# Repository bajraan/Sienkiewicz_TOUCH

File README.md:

# Sienkiewicz PCB

Sienkiewicz PCB project realized in KiCAD 9

> 🔗 Project main system repository: https://github.com/bajraan/Sienkiewicz__3ART00__SYSTEM

<h1 align="center">3ART12 TOUCH</h1>

<p align="center" width="100%">
  
</p>

***

<p align="center">
  
&nbsp; &nbsp; &nbsp; &nbsp;
  
</p>

***

## SPECIFICATIONS

| Parameter | Value | 
| --- | --- |
| Dimensions | 38.0 × 38.0 mm |

***

## DIRECTORY STRUCTURE

    .
    ├─ Computations       # Misc calculations
    ├─ HTML               # HTML files for generated webpage
    ├─ Images             # Pictures and renders
    │
    ├─ kibot_resources    # External resources for KiBot
    │  ├─ colors          # Color theme for KiCad
    │  ├─ fonts           # Fonts used in the project
    │  ├─ scripts         # External scripts used with KiBot
    │  └─ templates       # Templates for KiBot generated reports
    │
    ├─ kibot_yaml         # KiBot YAML config files
    ├─ KiRI               # KiRI (PCB diff viewer) files
    │
    ├─ lib                # KiCad footprint and symbol libraries
    │  ├─ 3d_models       # Component 3D models
    │  ├─ lib_fp          # Footprint libraries
    │  └─ lib_sym         # Symbol libraries
    │
    ├─ Logos              # Logos
    │
    ├─ Manufacturing      # Assembly and fabrication documents
    │  ├─ Assembly        # Assembly documents (BoM, pos, notes)
    │  │
    │  └─ Fabrication     # Fabrication documents (ZIP, notes)
    │     ├─ Drill Tables # CSV drill tables
    │     └─ Gerbers      # Gerbers
    │
    ├─ Report             # Reports for ERC/DRC
    ├─ Schematic          # PDF of schematic
    ├─ Templates          # Title block templates
    ├─ Testing
    │  └─ Testpoints      # Testpoints tables      
    │
    └─ Variants           # Outputs for assembly variants

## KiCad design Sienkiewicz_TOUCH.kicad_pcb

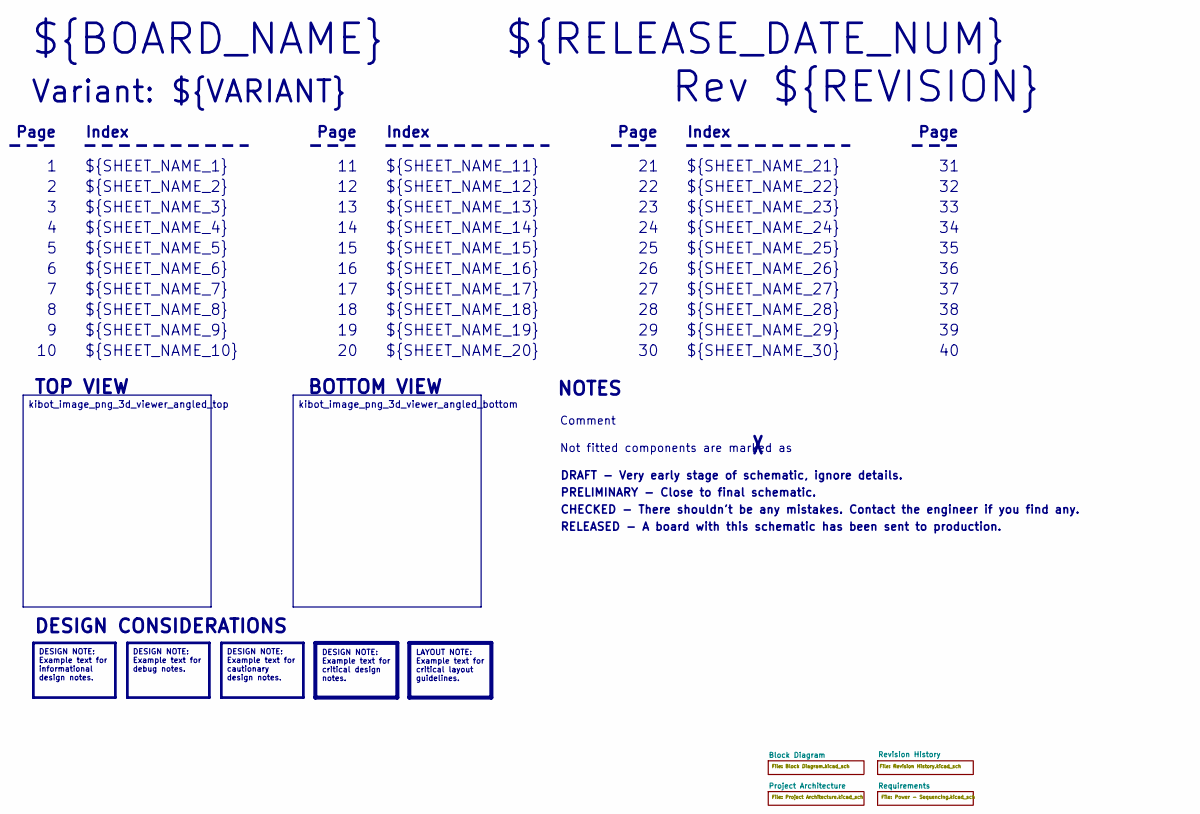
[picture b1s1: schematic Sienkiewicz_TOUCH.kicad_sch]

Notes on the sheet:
Variant: ${VARIANT}
RELEASED - A board with this schematic has been sent to production.
${SHEET_NAME_24}
Index
Page
PRELIMINARY - Close to final schematic.
${SHEET_NAME_22}
DRAFT - Very early stage of schematic, ignore details.
${SHEET_NAME_12}
${SHEET_NAME_8}
${SHEET_NAME_2}
${SHEET_NAME_5}
${SHEET_NAME_20}
${SHEET_NAME_23}
${RELEASE_DATE_NUM}
Not fitted components are marked as
${SHEET_NAME_11}
${SHEET_NAME_6}
${SHEET_NAME_26}
Rev ${REVISION}
${SHEET_NAME_15}
CHECKED - There shouldn't be any mistakes. Contact the engineer if you find any.
BOTTOM VIEW
${SHEET_NAME_14}
${SHEET_NAME_21}
${SHEET_NAME_17}
${SHEET_NAME_18}
${SHEET_NAME_7}
${BOARD_NAME}
NOTES
${SHEET_NAME_1}
${SHEET_NAME_9}
${SHEET_NAME_29}
${SHEET_NAME_16}
${SHEET_NAME_3}
${SHEET_NAME_19}
Comment
TOP VIEW
${SHEET_NAME_10}
${SHEET_NAME_28}

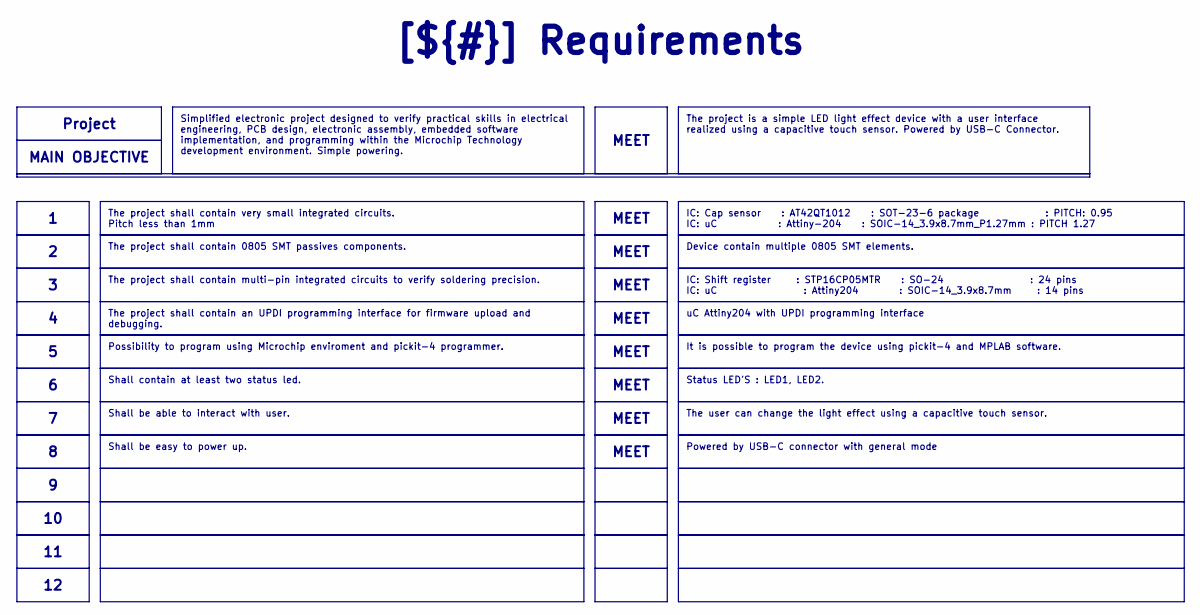
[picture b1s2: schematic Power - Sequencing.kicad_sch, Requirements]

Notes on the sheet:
Powered by USB-C connector with general mode
IC: Cap sensor : AT42QT1012 : SOT-23-6 package : PITCH: 0.95 IC: uC : Attiny-204 : SOIC-14_3.9x8.7mm_P1.27mm : PITCH 1.27
Simplified electronic project designed to verify practical skills in electrical engineering, PCB design, electronic assembly, embedded software implementation, and programming within the Microchip Technology development environment. Simple powering.
Shall contain at least two status led.
The project shall contain very small integrated circuits. Pitch less than 1mm
uC Attiny204 with UPDI programming interface
Status LED'S : LED1, LED2.
MEET
Shall be easy to power up.
Project
The project shall contain an UPDI programming interface for firmware upload and debugging.
[${#}] ${TITLE}
IC: Shift register : STP16CP05MTR : SO-24 : 24 pins IC: uC : Attiny204 : SOIC-14_3.9x8.7mm : 14 pins
It is possible to program the device using pickit-4 and MPLAB software.
MAIN OBJECTIVE
The user can change the light effect using a capacitive touch sensor.
The project shall contain multi-pin integrated circuits to verify soldering precision.
The project shall contain 0805 SMT passives components.
Device contain multiple 0805 SMT elements.
Possibility to program using Microchip enviroment and pickit-4 programmer.
Shall be able to interact with user.
The project is a simple LED light effect device with a user interface realized using a capacitive touch sensor. Powered by USB-C Connector.

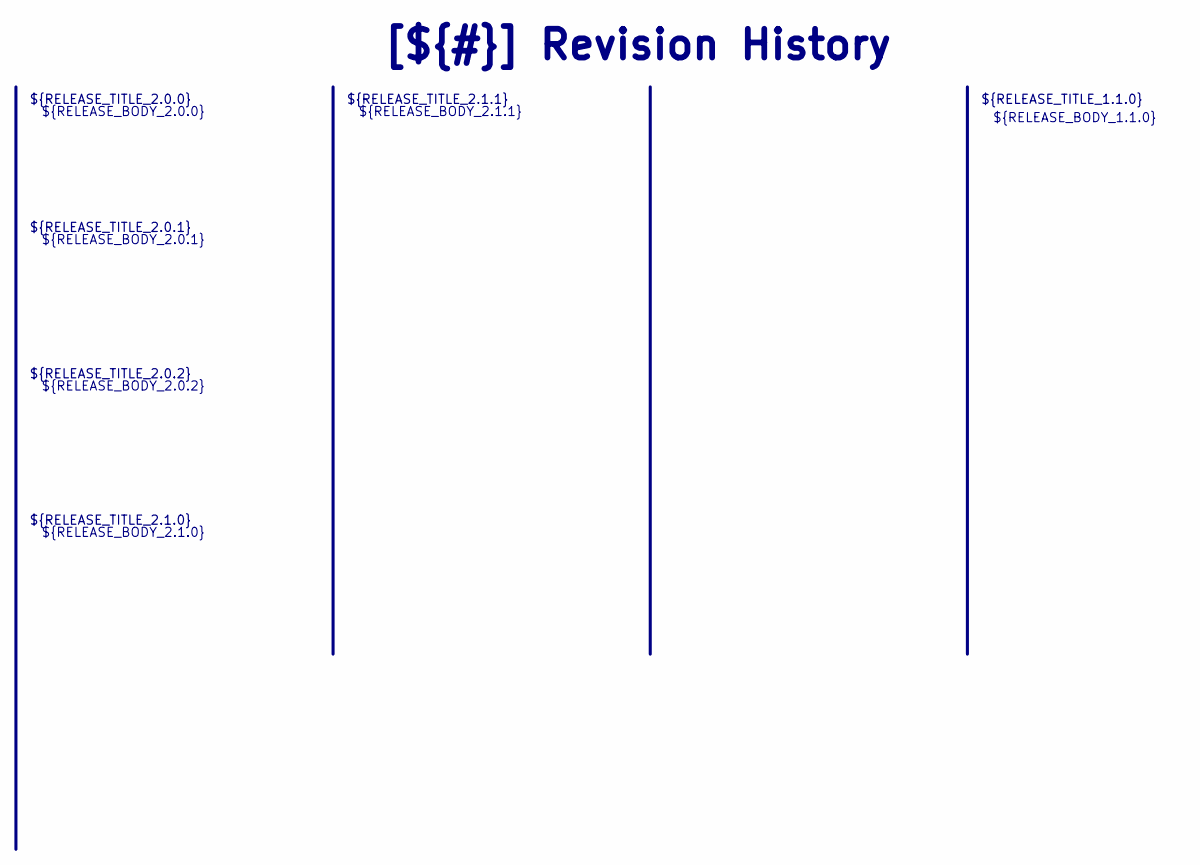
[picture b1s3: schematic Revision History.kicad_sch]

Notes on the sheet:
${RELEASE_BODY_1.1.0}
${RELEASE_BODY_2.1.1}
[${#}] ${TITLE}
${RELEASE_BODY_2.0.0}
${RELEASE_TITLE_2.1.1}
${RELEASE_BODY_2.1.0}
${RELEASE_TITLE_2.0.2}
${RELEASE_TITLE_2.1.0}
${RELEASE_BODY_2.0.2}
${RELEASE_BODY_2.0.1}
${RELEASE_TITLE_2.0.0}
${RELEASE_TITLE_2.0.1}
${RELEASE_TITLE_1.1.0}

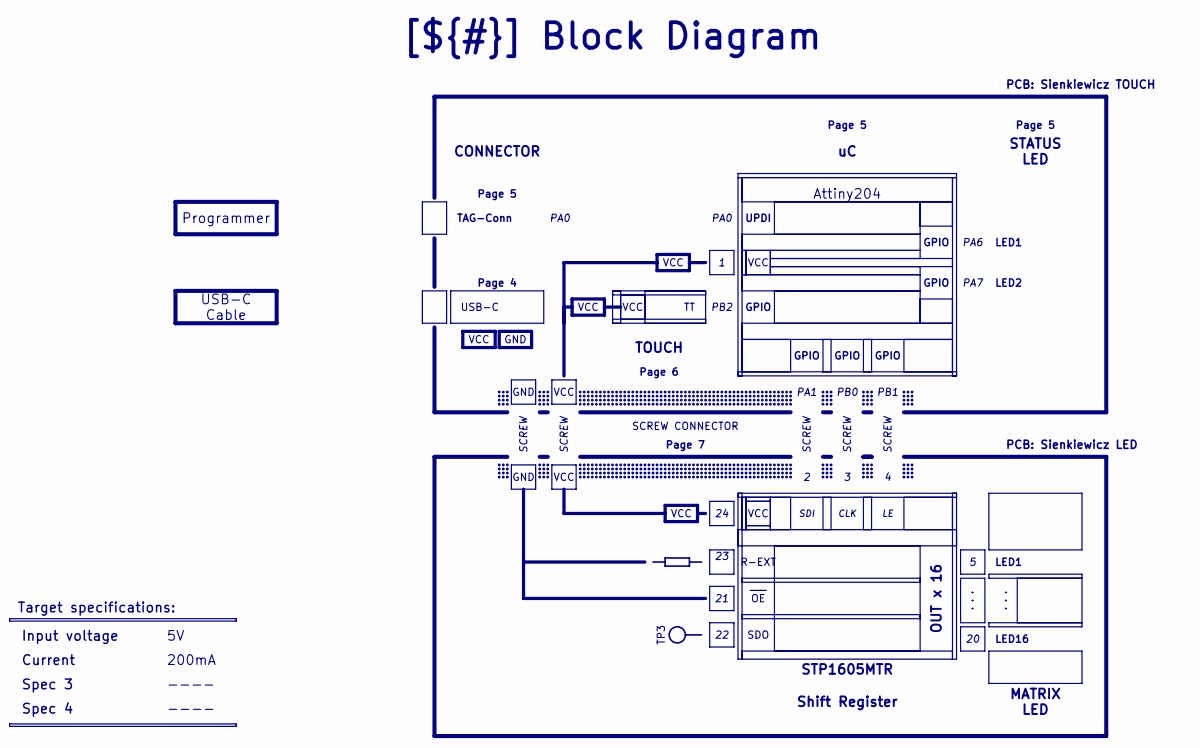
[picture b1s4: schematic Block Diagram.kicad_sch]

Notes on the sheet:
PCB: Sienkiewicz LED
PCB: Sienkiewicz TOUCH
TP3
PB1
Page 5
STATUS LED
GND
. . .
Spec 4
LED2
VCC
USB-C Cable
----
STP1605MTR
SCREW
GPIO
LED1
R-EXT
TAG-Conn
PA7
Shift Register
CLK
[${#}] ${TITLE}
200mA
Input voltage
TOUCH
Page 6
CONNECTOR
SCREW CONNECTOR
Target specifications:
Programmer
Attiny204
Page 4
PA1
Spec 3
MATRIX LED
Current
Page 7
PB0
PA0

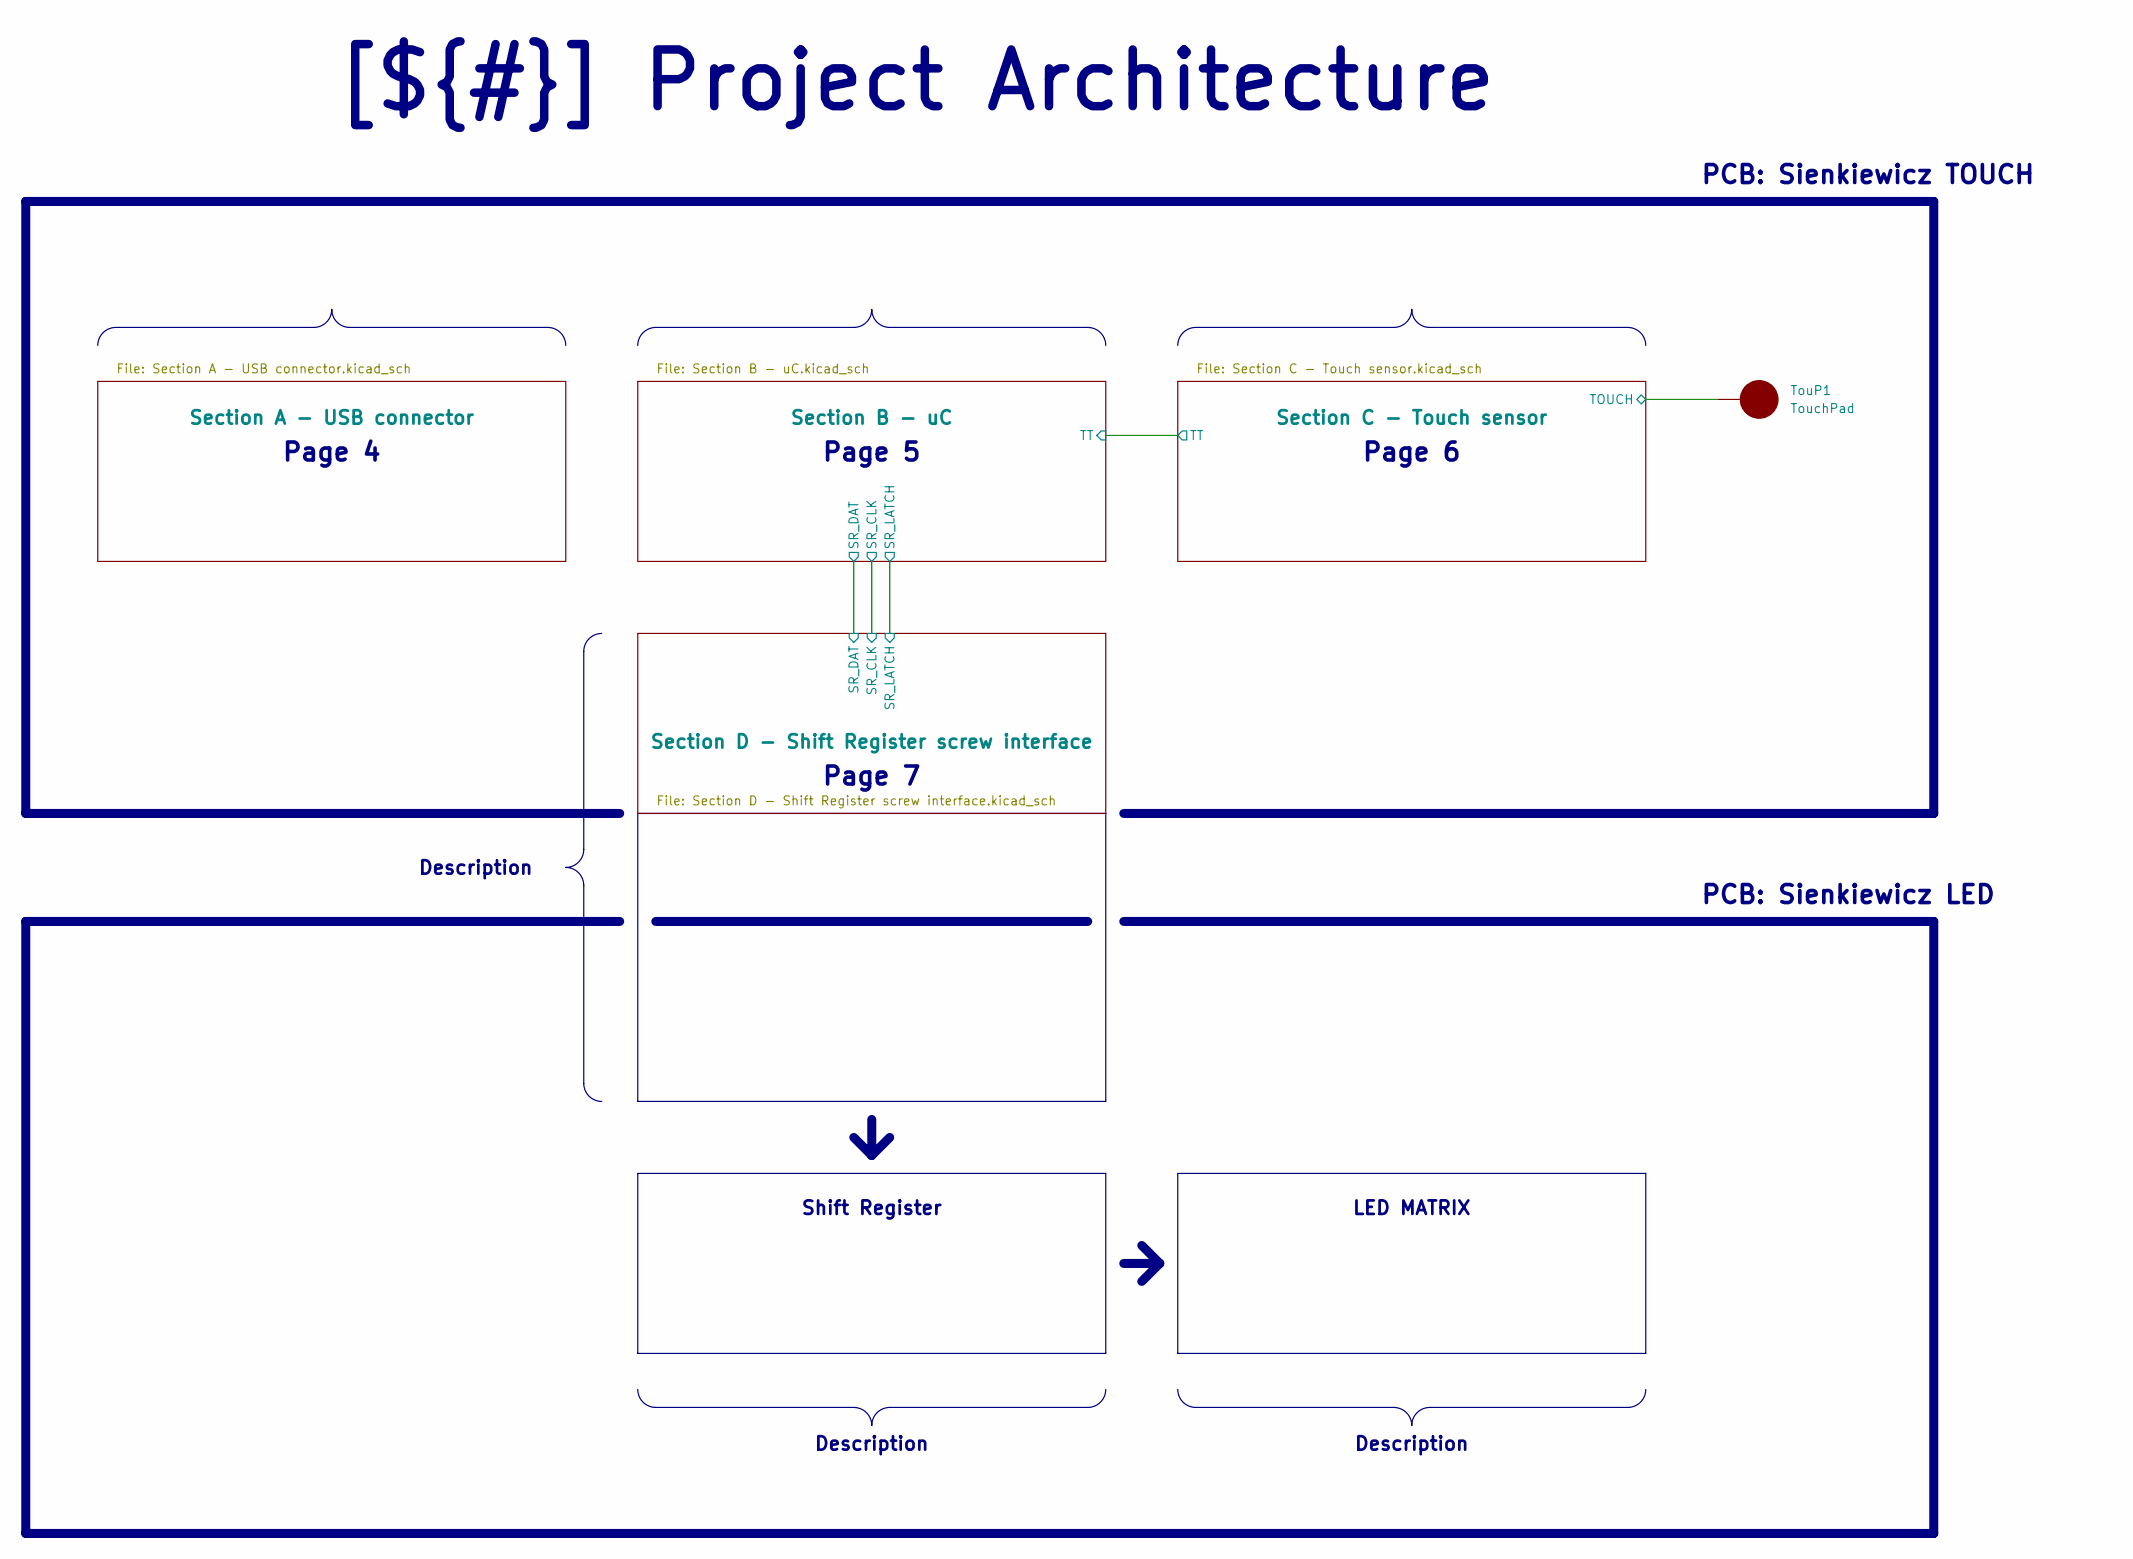
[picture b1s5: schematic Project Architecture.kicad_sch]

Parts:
TouP1: TouchPad; TouchPAD

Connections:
/Project Architecture/Section C - Touch sensor/TOUCH: TouP1.1 (TOUCH); also elsewhere on the board

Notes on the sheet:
LED MATRIX
Page 6
Shift Register
Page 7
Page 5
PCB: Sienkiewicz LED
PCB: Sienkiewicz TOUCH
Page 4
Description
[${#}] ${TITLE}

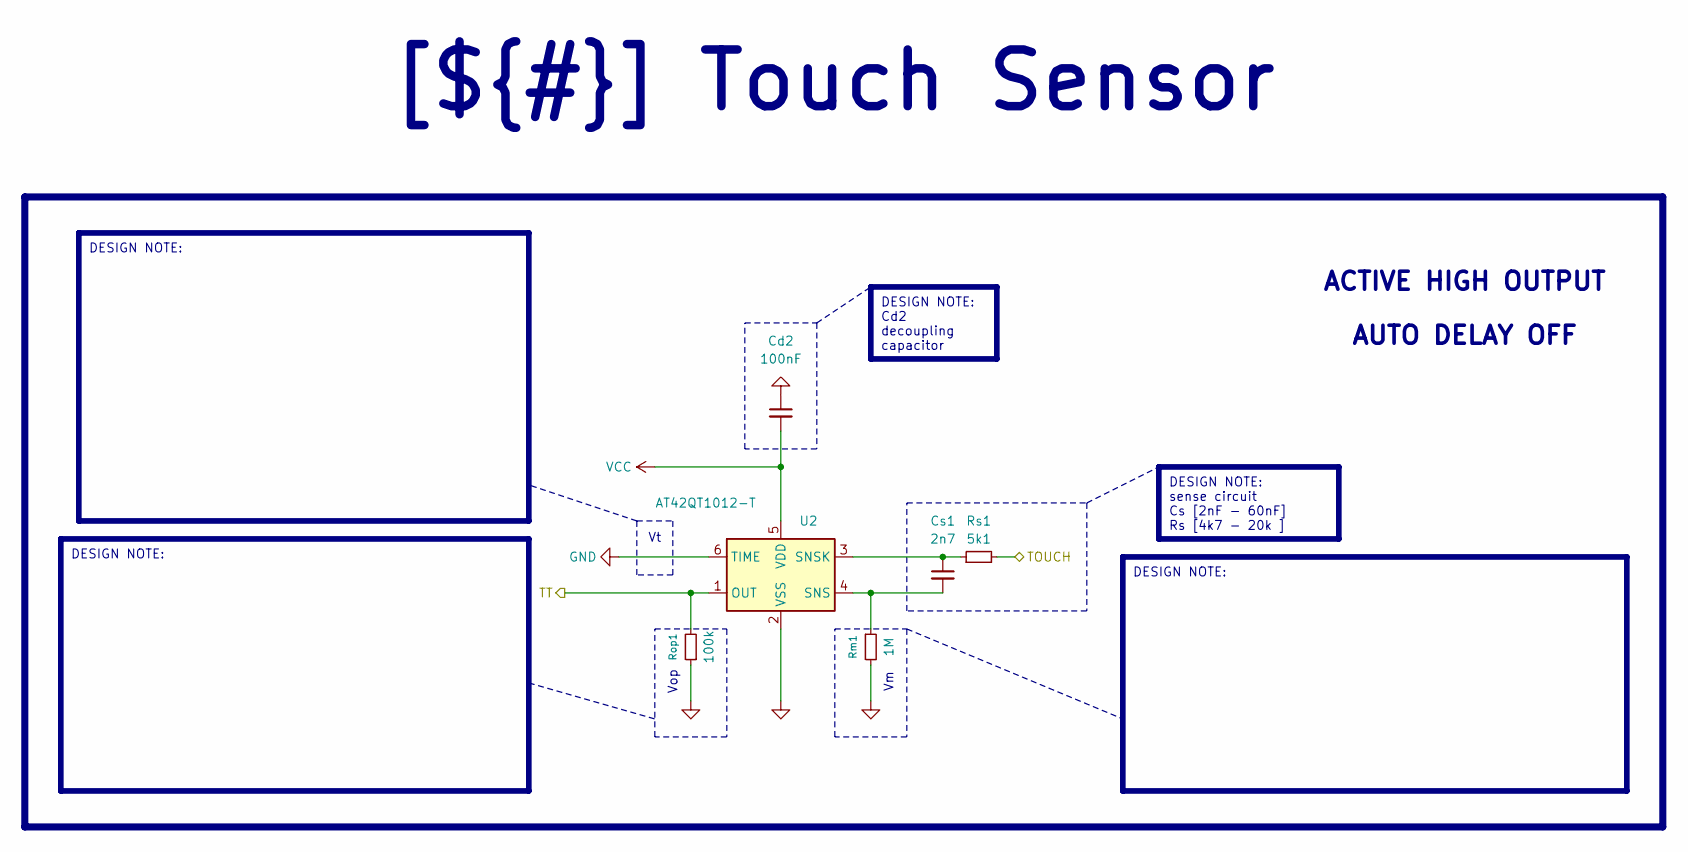
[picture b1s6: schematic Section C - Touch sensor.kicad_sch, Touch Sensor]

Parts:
Cd2: 100nF; C_1210_3225Metric
Cs1: 2n7; C_0805_2012Metric
Rm1: 1M; R_0805_2012Metric
Rop1: 100k; R_0805_2012Metric
Rs1: 5k1; R_0805_2012Metric
U2: AT42QT1012-T; SOT-23-6

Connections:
/Project Architecture/Section B - uC/TT: Rop1.2, U2.1 (OUT); also elsewhere on the board
/Project Architecture/Section C - Touch sensor/TOUCH: Rs1.2; also elsewhere on the board
GND: Cd2.1, Rm1.2, Rop1.1, U2.2 (VSS), U2.6 (TIME); also elsewhere on the board
unnamed: Cs1.2, Rm1.1, U2.4 (SNS)
unnamed: Cs1.1, Rs1.1, U2.3 (SNSK)
VCC: Cd2.2, U2.5 (VDD); also elsewhere on the board

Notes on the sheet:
Vop
DESIGN NOTE:
DESIGN NOTE: Cd2 decoupling capacitor
[${#}] ${TITLE}
DESIGN NOTE:
AUTO DELAY OFF
DESIGN NOTE: sense circuit Cs [2nF - 60nF] Rs [4k7 - 20k ]
ACTIVE HIGH OUTPUT

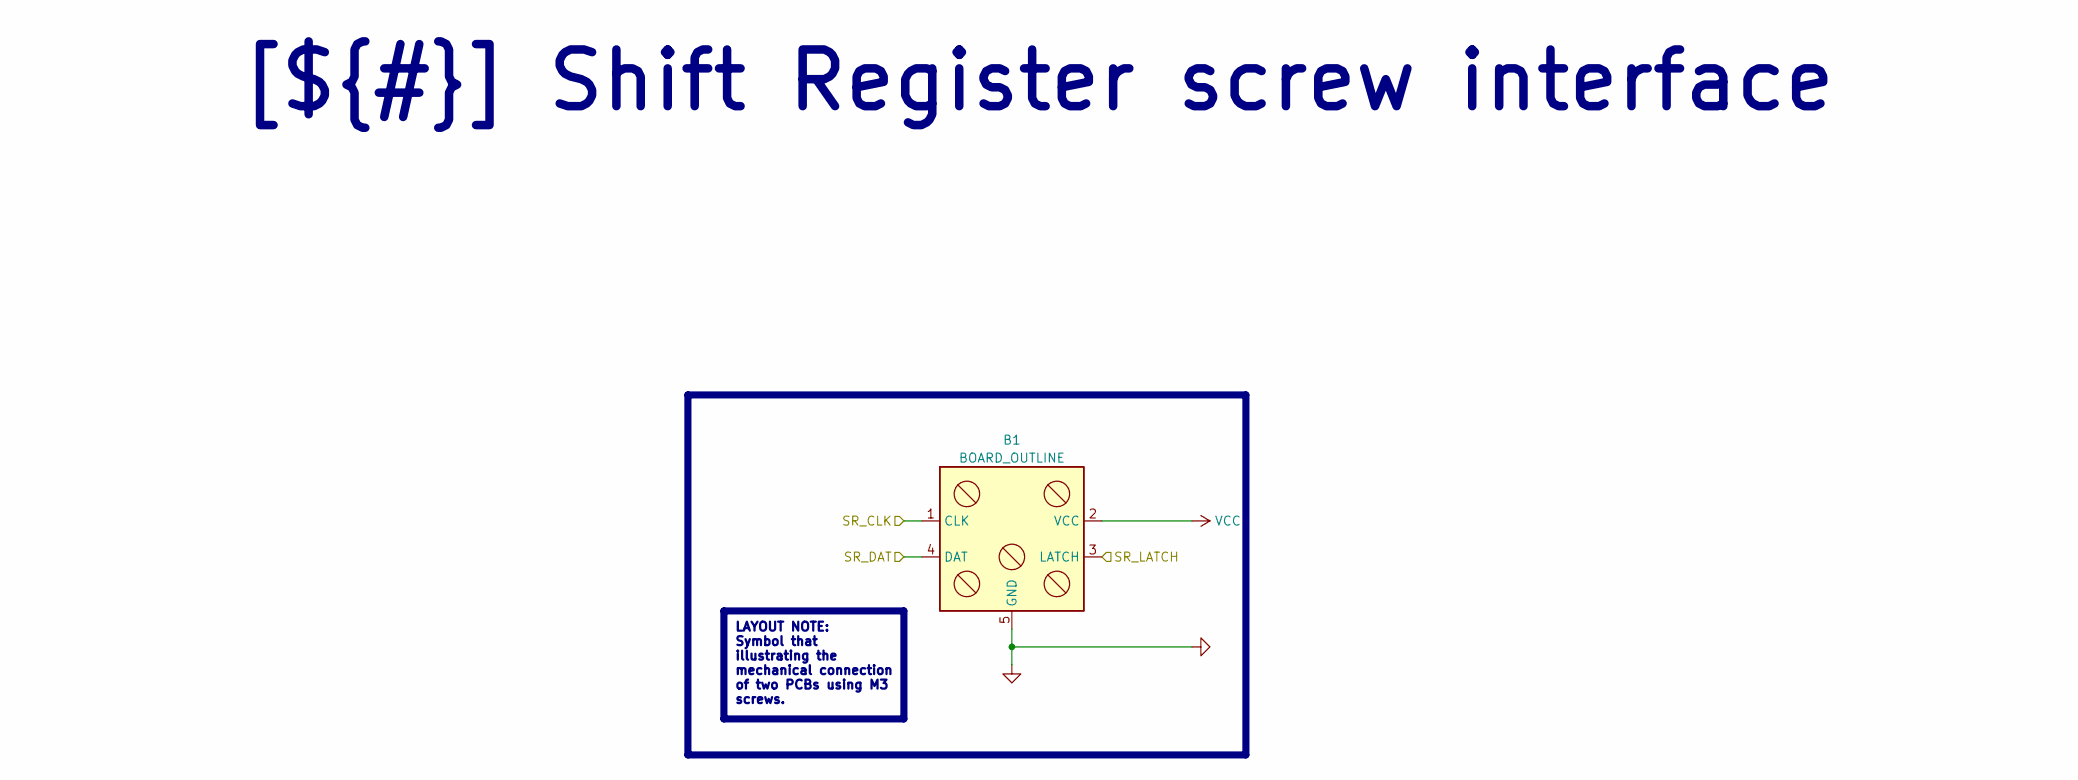
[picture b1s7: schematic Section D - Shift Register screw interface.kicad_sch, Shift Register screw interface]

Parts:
B1: BOARD_OUTLINE; Sienkiewicz

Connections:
/Project Architecture/Section B - uC/SR_CLK: B1.1 (CLK); also elsewhere on the board
/Project Architecture/Section B - uC/SR_DAT: B1.4 (DAT); also elsewhere on the board
/Project Architecture/Section B - uC/SR_LATCH: B1.3 (LATCH); also elsewhere on the board
GND: B1.5 (GND); also elsewhere on the board
VCC: B1.2 (VCC); also elsewhere on the board

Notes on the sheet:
LAYOUT NOTE: Symbol that illustrating the mechanical connection of two PCBs using M3 screws.
[${#}] ${TITLE}

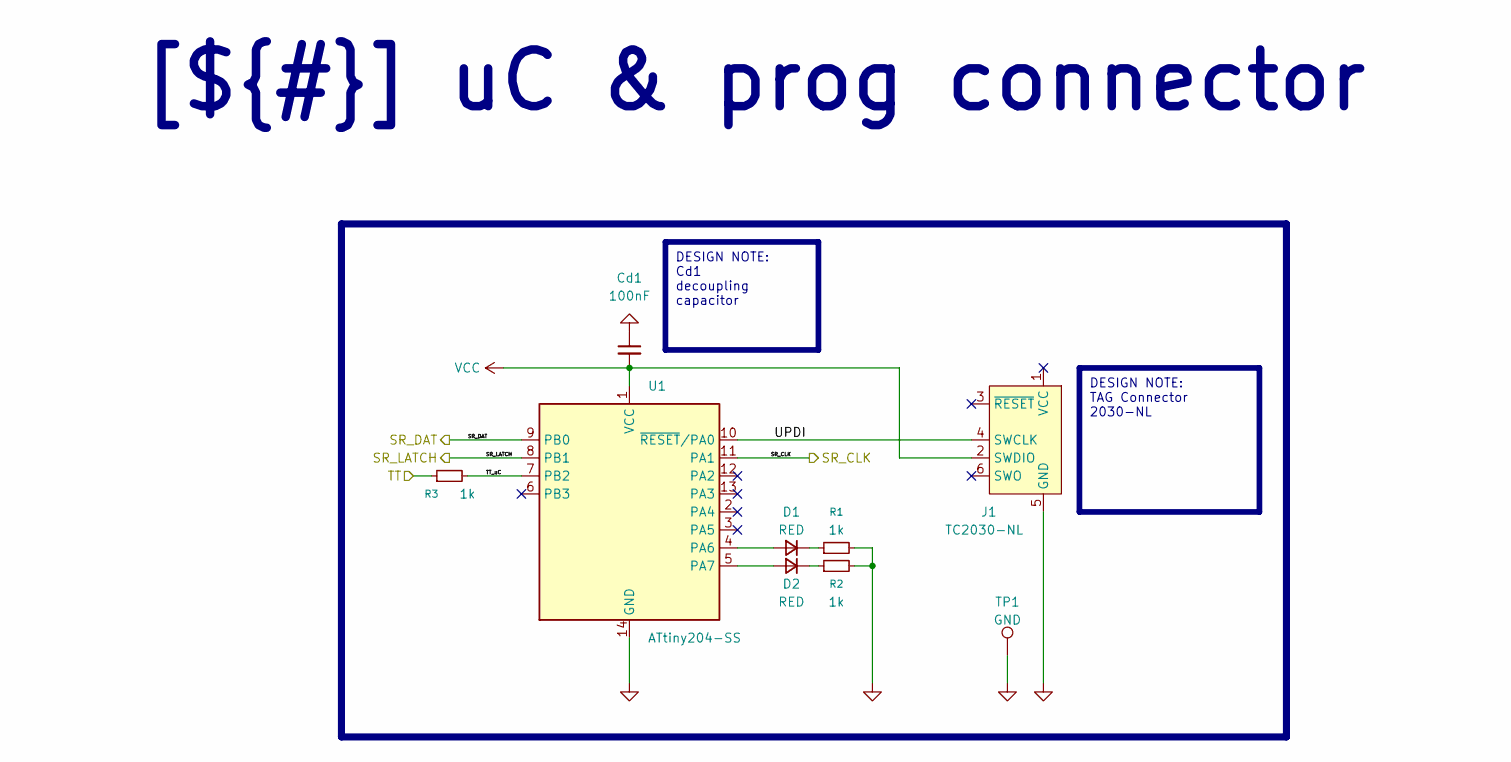
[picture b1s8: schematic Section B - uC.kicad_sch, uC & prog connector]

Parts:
Cd1: 100nF; C_1210_3225Metric
D1, D2: RED; LED_1206_3216Metric
J1: TC2030-NL; Tag-Connect_TC2030-IDC-NL_2x03_P1.27mm_Vertical
R1, R2, R3: 1k; R_0805_2012Metric
TP1: GND; TestPoint_Pad_D1.5mm
U1: ATtiny204-SS; SOIC-14_3.9x8.7mm_P1.27mm

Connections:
/Project Architecture/Section B - uC/SR_CLK: U1.11 (PA1); also elsewhere on the board
/Project Architecture/Section B - uC/SR_DAT: U1.9 (PB0); also elsewhere on the board
/Project Architecture/Section B - uC/SR_LATCH: U1.8 (PB1); also elsewhere on the board
/Project Architecture/Section B - uC/TT: R3.1; also elsewhere on the board
/Project Architecture/Section B - uC/TT_uC: R3.2, U1.7 (PB2)
/Project Architecture/Section B - uC/UPDI: J1.4 (SWCLK), U1.10 (~RESET/PA0)
GND: Cd1.1, J1.5 (GND), R1.2, R2.2, TP1.1, U1.14 (GND); also elsewhere on the board
unnamed: D1.2 (A), U1.4 (PA6)
unnamed: D1.1 (K), R1.1
unnamed: D2.2 (A), U1.5 (PA7)
unnamed: D2.1 (K), R2.1
VCC: Cd1.2, J1.2 (SWDIO), U1.1 (VCC); also elsewhere on the board

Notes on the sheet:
[${#}] ${TITLE}
DESIGN NOTE: Cd1 decoupling capacitor
DESIGN NOTE: TAG Connector 2030-NL

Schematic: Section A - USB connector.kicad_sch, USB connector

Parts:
Cb1, Cb2: 1u/16V; C_0805_2012Metric
J2: USB4135-GF-A_REVA; GCT_USB4135-GF-A_REVA; PARTREV A; DigiKey_Part_Number 2073-USB4135-GF-ATR-ND
Rd1, Rd2: 5k1; R_0805_2012Metric

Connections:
GND: Cb1.1, Cb2.1, J2.A12 (GND_A), J2.B12 (GND_B), Rd1.2, Rd2.2; also elsewhere on the board
unnamed: J2.A5 (CC), Rd1.1
unnamed: J2.B5 (VCONN), Rd2.1
VCC: Cb1.2, Cb2.2, J2.A9 (VBUS_A), J2.B9 (VBUS_B); also elsewhere on the board

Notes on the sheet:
www.usb.org/sites/default/files/USB%20Type-C%20Spec%20R2.0%20-%20August%202019.pdf
J. Pieper ADC investigation
STM32G474 Datasheet p.81
AN5346
DESIGN NOTE: Cb1, Cb2 bulk capacitor
[${#}] ${TITLE}
DESIGN NOTE: Per USB-IF specification, a sink role is established by placing 5.1 kΩ pull-down (Rd) resistors on CC1 and CC2.

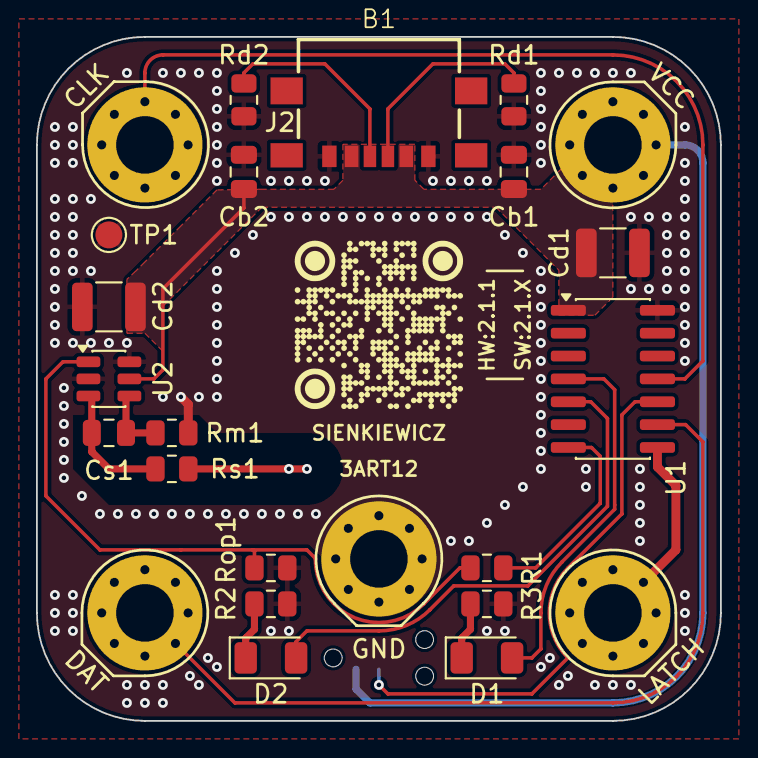
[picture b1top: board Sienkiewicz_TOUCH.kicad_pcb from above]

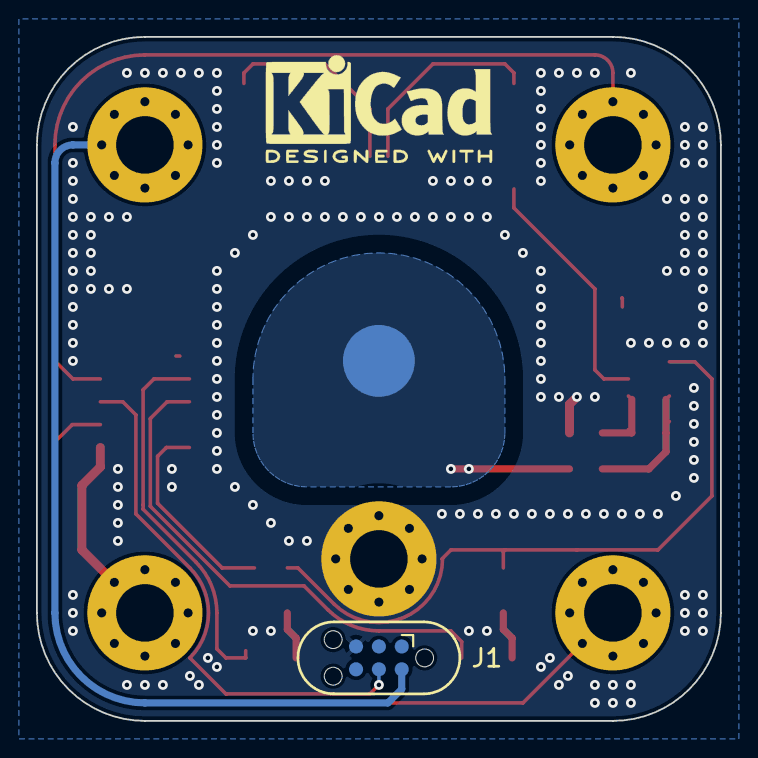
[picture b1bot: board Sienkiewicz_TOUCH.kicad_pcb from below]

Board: 2 copper layers, 38.0 x 38.0 mm, 22 parts (2 on the bottom side), 17 nets.

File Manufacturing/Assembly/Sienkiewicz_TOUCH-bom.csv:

Row,Quantity Per PCB,References,Value,Datasheet,Footprint,Description,Manufacturer,Manufacturer Part Number,Supplier Part Number,BOM_STATUS,BOM_INFO
1,1,B1,BOARD_OUTLINE,,Sienkiewicz,,,,,N/A,N/A
2,2,Cb1 Cb2,1u/16V,~,C_0805_2012Metric,Unpolarized capacitor,,,,OK,TME BOX
3,2,Cd1 Cd2,100nF,~,C_1210_3225Metric,"Unpolarized capacitor, small symbol",,,,OK,AIDATEK A0
4,1,Cs1,2n7,~,C_0805_2012Metric,"Unpolarized capacitor, small symbol",,,,OK,TME BOX
5,2,D1 D2,RED,~,LED_1206_3216Metric,"Diode, small symbol",,,,OK,AIDATEK A0
6,1,J2,USB4135-GF-A_REVA,,GCT_USB4135-GF-A_REVA,,GCT,,,OK,TME BOX
7,3,R1 R2 R3,1k,~,R_0805_2012Metric,"Resistor, small symbol",,,,OK,AIDATEK A0
8,3,Rd1 Rd2 Rs1,5k1,~,R_0805_2012Metric,"Resistor, small symbol",,,,OK,TME BOX 25.06.2025
9,1,Rm1,1M,~,R_0805_2012Metric,"Resistor, small symbol",,,,OK,TME BOX
10,1,Rop1,100k,~,R_0805_2012Metric,"Resistor, small symbol",,,,OK,TME BOX
11,1,TouP1,TouchPad,~,TouchPAD,touch pad,,,,N/A,N/A
12,1,U2,AT42QT1012-T,http://ww1.microchip.com/downloads/en/DeviceDoc/40001948A.pdf,SOT-23-6,"Single-Key Touch Sensor IC, SOT-23-6",,,,OK,TME BOX
13,1,U1,ATtiny204-SS,http://ww1.microchip.com/downloads/en/DeviceDoc/50002687A.pdf,SOIC-14_3.9x8.7mm_P1.27mm,"20MHz, 2kB Flash, 128B SRAM, 64B EEPROM, SOIC-14",,,,OK,AIDATEK A1

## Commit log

2026-04-13 kibot yaml update
2026-04-13 schematic file names changed
2026-04-13 Update Outputs
2026-04-13 preliminary phase
2026-04-13 sienkiewicz library missing value update
2026-04-14 board updatea
2026-04-14 pcb update
2026-04-14 pcv update
2026-04-15 led1,led2 better documented
2026-04-15 kicad_prl update
2026-04-15 .kicad_pro resolve problems
2026-04-15 touch pad library creation
2026-04-16 minor updates of shematic and pcb and touch pad library
2026-04-16 [sch] update touch sensor section
2026-04-17 screw interface update - changed pinout
2026-04-17 refresh
2026-04-18 [CFG] Configuration update, added bom information fields
2026-04-18 bom update, qr-code added
2026-04-18 kibot kiri config update
2026-04-20 [sch] added R3 to prevent high current drain from cap touch chip
2026-04-24 [pcb] board outline/connection changed / back compatibility not possible
2026-04-24 project structure cleaning from old files
2026-04-24 file refresh
2026-04-24 [pcb] checked
2026-04-24 VCC and GND chierarchical labels added
2026-04-24 moved the label to force push from local repo
2026-04-24 .gitattributes add binary information and -ours flag
2026-04-24 Update CHANGELOG
2026-04-24 Update Outputs (release)
2026-04-24 restore .gitattributes to base version
2026-04-24 descriptions on the board update
2026-04-25 missing file added QR code 10x10
2026-04-25 prepared for 2.0.1 release
2026-04-25 fix .yaml file
2026-04-25 silkscreen, centered LATCH outlie on screw connector
2026-04-25 [pcb] silkscreen, version bump to 2.0.1
2026-04-25 [pcb] fabrication layers update
2026-04-25 prep for 2.0.2 release
2026-04-27 changed signal layer names for JLCPCB naming convention
2026-04-30 [cfg] update kibot configuration project properties
2026-04-30 initial prep for SR signals reassignment (refs #4)
2026-04-30 reassign SR signals for clean design (fixes #4)
2026-04-30 revision history update, prep for V2.1.0 relese
2026-04-30 revisiion history.kicad_sch update
2026-05-01 changelod fix
2026-05-12 gitignore stencil folder
2026-05-21 documentation update / block diagram
2026-05-21 removed hierarhical vcc labels
2026-05-21 routing update #4
2026-05-21 documentation update /requirements /schematic
2026-05-21 trying to resolve the issue with tex box
2026-05-21 prep for 2.1.1 release
2026-05-21 2.1.1 fixes #4
2026-06-08 readme.md update
2026-06-11 schematic update
2026-06-11 schematid update - block diagram fix
